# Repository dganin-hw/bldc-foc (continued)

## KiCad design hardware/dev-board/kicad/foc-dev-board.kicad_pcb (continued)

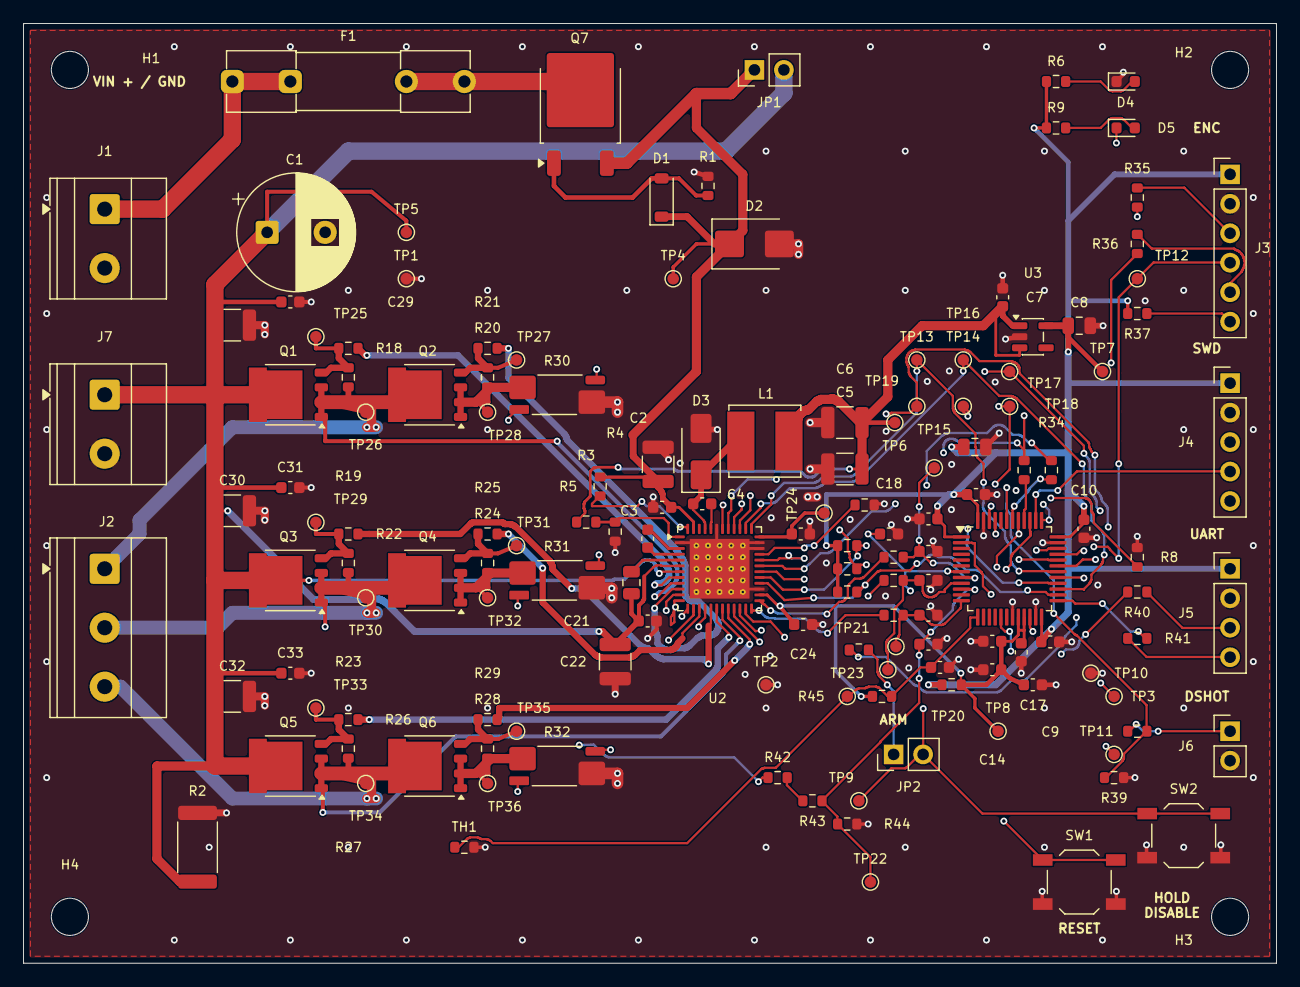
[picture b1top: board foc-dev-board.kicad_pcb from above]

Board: 4 copper layers, 108.0 x 81.0 mm, 149 parts (0 on the bottom side), 83 nets.

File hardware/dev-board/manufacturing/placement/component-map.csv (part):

Reference,Value,MPN_or_assembly,Footprint,X_from_left_mm,Y_from_top_mm,KiCad_angle_deg,Side,Physical_BOM,DNP,Note
C1,470u / 35V low ESR,EEUFR1V471,Capacitor_THT:CP_Radial_D10.0mm_P5.00mm,21.0,18.0,0.0,TOP,True,False,"Panasonic FR, 470uF 35V, D10 x H16 mm, lead pitch 5mm; 0.6mm leads."
C10,100n / 10V,CL10B104KB8NNNC,Capacitor_SMD:C_0603_1608Metric,91.4,43.55,-90.0,TOP,True,False,
C11,100n / 10V,CL10B104KB8NNNC,Capacitor_SMD:C_0603_1608Metric,82.1,40.6,0.0,TOP,True,False,
C12,100n / 10V,CL10B104KB8NNNC,Capacitor_SMD:C_0603_1608Metric,78.0,42.7,180.0,TOP,True,False,
C13,4.7u / 10V,CL21B475KPFNNNE,Capacitor_SMD:C_0805_2012Metric,82.0,36.5,0.0,TOP,True,False,
C14,1u / 10V,CL10B105KO8NNNC,Capacitor_SMD:C_0603_1608Metric,83.5,55.7,180.0,TOP,True,False,
C15,100n / 10V,CL10B104KB8NNNC,Capacitor_SMD:C_0603_1608Metric,83.5,53.25,180.0,TOP,True,False,At VDDA pin 21.
C16,100n / 10V,CL10B104KB8NNNC,Capacitor_SMD:C_0603_1608Metric,86.0,54.2,-90.0,TOP,True,False,At VREF+ pin 20.
C17,1u / 10V,CL10B105KO8NNNC,Capacitor_SMD:C_0603_1608Metric,87.0,57.0,0.0,TOP,True,False,At VREF+ pin 20.
C18,100n / 10V,CL10B104KB8NNNC,Capacitor_SMD:C_0603_1608Metric,74.6,44.0,0.0,TOP,True,False,
C19,47n / 50V X7R,CL10B473KB8NNNC,Capacitor_SMD:C_0603_1608Metric,53.8,44.4,90.0,TOP,True,False,
C2,4.7u / 50V X7R,GRM32ER71H475KA88L,Capacitor_SMD:C_1210_3225Metric,54.7,38.0,90.0,TOP,True,False,
C20,1u / 25V X7R,CL21B105KAFNNNE,Capacitor_SMD:C_0805_2012Metric,52.4,48.2,-90.0,TOP,True,False,
C21,100n / 50V,CL10B104KB8NNNC,Capacitor_SMD:C_0603_1608Metric,53.8,51.5,0.0,TOP,True,False,
C22,10u / 50V X7R,GRM32ER71H106KA12L,Capacitor_SMD:C_1210_3225Metric,51.0,55.0,-90.0,TOP,True,False,
C23,1u / 10V,CL10B105KO8NNNC,Capacitor_SMD:C_0603_1608Metric,67.0,44.0,0.0,TOP,True,False,
C24,100n / 10V,CL10B104KB8NNNC,Capacitor_SMD:C_0603_1608Metric,67.2,51.8,0.0,TOP,True,False,
C25,1n / C0G,GRM1885C1H102JA01D,Capacitor_SMD:C_0603_1608Metric,78.0,45.5,0.0,TOP,True,False,
C26,1n / C0G,GRM1885C1H102JA01D,Capacitor_SMD:C_0603_1608Metric,78.0,51.0,0.0,TOP,True,False,
C27,1n / C0G,GRM1885C1H102JA01D,Capacitor_SMD:C_0603_1608Metric,78.0,48.0,0.0,TOP,True,False,
C28,4.7u / 50V X7R,GRM32ER71H475KA88L,Capacitor_SMD:C_1210_3225Metric,18.0,26.0,0.0,TOP,True,False,
C29,100n / 50V,CL10B104KB8NNNC,Capacitor_SMD:C_0603_1608Metric,23.0,24.0,0.0,TOP,True,False,
C3,100n / 50V,CL10B104KB8NNNC,Capacitor_SMD:C_0603_1608Metric,55.05,41.7,180.0,TOP,True,False,
C30,4.7u / 50V X7R,GRM32ER71H475KA88L,Capacitor_SMD:C_1210_3225Metric,18.0,42.0,0.0,TOP,True,False,
C31,100n / 50V,CL10B104KB8NNNC,Capacitor_SMD:C_0603_1608Metric,23.0,40.0,0.0,TOP,True,False,
C32,4.7u / 50V X7R,GRM32ER71H475KA88L,Capacitor_SMD:C_1210_3225Metric,18.0,58.0,0.0,TOP,True,False,
C33,100n / 50V,CL10B104KB8NNNC,Capacitor_SMD:C_0603_1608Metric,23.0,56.0,0.0,TOP,True,False,
C34,10n / 50V,CL10B103KB8NNNC,Capacitor_SMD:C_0603_1608Metric,78.0,53.5,0.0,TOP,True,False,
C35,10n / 10V,CL10B103KB8NNNC,Capacitor_SMD:C_0603_1608Metric,79.0,55.5,0.0,TOP,True,False,
C4,100n / 25V,CL10B104KB8NNNC,Capacitor_SMD:C_0603_1608Metric,58.5,41.4,180.0,TOP,True,False,
C5,22u / 16V X7R,CL32B226KAJNNNE,Capacitor_SMD:C_1210_3225Metric,70.8,34.4,180.0,TOP,True,False,
C6,22u / 16V X7R,CL32B226KAJNNNE,Capacitor_SMD:C_1210_3225Metric,70.8,38.4,180.0,TOP,True,False,
C7,1u / 10V,CL10B105KO8NNNC,Capacitor_SMD:C_0603_1608Metric,84.4,23.6,90.0,TOP,True,False,
C8,4.7u / 10V,CL21B475KPFNNNE,Capacitor_SMD:C_0805_2012Metric,91.0,26.05,0.0,TOP,True,False,
C9,100n / 10V,CL10B104KB8NNNC,Capacitor_SMD:C_0603_1608Metric,88.5,53.3,0.0,TOP,True,False,
D1,BZT52C12,BZT52C12-7-F,Diode_SMD:D_SOD-123,55.0,15.0,90.0,TOP,True,False,12 V VGS clamp; cathode at PMOS source.
D2,SMBJ18A,SMBJ18A,Diode_SMD:D_SMB,63.0,19.0,0.0,TOP,True,False,"Input transient clamp, NOT a continuous braking resistor."
D3,SS16,SS16,Diode_SMD:D_SMA,58.4,36.9,90.0,TOP,True,False,
D4,POWER green,LTST-C190KGKT,LED_SMD:LED_0603_1608Metric,95.0,5.0,0.0,TOP,True,False,
D5,STATUS green,LTST-C190KGKT,LED_SMD:LED_0603_1608Metric,95.0,9.0,0.0,TOP,True,False,
F1,2A fast / DC-rated,BK1/S501-2-R + 01110005MR x2,Fuse:Fuseholder_Clip-5x20mm_Littelfuse_111_Inline_P20.00x5.00mm_D1.05mm_Horizontal,18.0,5.0,0.0,TOP,True,False,"Assembly: two Littelfuse 111 clips plus one Eaton BK1/S501-2-R, 2A fast 5x20mm cartridge; not a phase-current limiter."
H1,M3 NPTH,,MountingHole:MountingHole_3.2mm_M3,4.0,4.0,0.0,TOP,False,False,
H2,M3 NPTH,,MountingHole:MountingHole_3.2mm_M3,104.0,4.0,0.0,TOP,False,False,
H3,M3 NPTH,,MountingHole:MountingHole_3.2mm_M3,104.0,77.0,0.0,TOP,False,False,
H4,M3 NPTH,,MountingHole:MountingHole_3.2mm_M3,4.0,77.0,0.0,TOP,False,False,
J1,VIN 12V / GND,1715721,"TerminalBlock_Phoenix:TerminalBlock_Phoenix_MKDS-1,5-2-5.08_1x02_P5.08mm_Horizontal",7.0,16.0,-90.0,TOP,True,False,Phoenix MKDS 1.5/2-5.08; wire entry faces board left edge.
J2,MOTOR A / B / C,1715734,"TerminalBlock_Phoenix:TerminalBlock_Phoenix_MKDS-1,5-3-5.08_1x03_P5.08mm_Horizontal",7.0,47.0,-90.0,TOP,True,False,Phoenix MKDS 1.5/3-5.08; wire entry faces board left edge.
J3,ENC 3V3 GND SCK MISO MOSI CS,B-2100S06P-A110,Connector_PinHeader_2.54mm:PinHeader_1x06_P2.54mm_Vertical,104.0,13.0,0.0,TOP,True,False,
J4,SWD VTREF GND IO CLK RESET,B-2100S05P-A110,Connector_PinHeader_2.54mm:PinHeader_1x05_P2.54mm_Vertical,104.0,31.0,0.0,TOP,True,False,
J5,UART 3V3 GND TX RX,B-2100S04P-A110,Connector_PinHeader_2.54mm:PinHeader_1x04_P2.54mm_Vertical,104.0,47.0,0.0,TOP,True,False,
J6,DSHOT / GND,B-2100S02P-A110,Connector_PinHeader_2.54mm:PinHeader_1x02_P2.54mm_Vertical,104.0,61.0,0.0,TOP,True,False,
J7,EXTERNAL BUS LOAD,1715721,"TerminalBlock_Phoenix:TerminalBlock_Phoenix_MKDS-1,5-2-5.08_1x02_P5.08mm_Horizontal",7.0,32.0,-90.0,TOP,True,False,External VM/GND load connection; braking load is not included.
JP1,BRIDGE POWER LINK,B-2100S02P-A110,Connector_PinHeader_2.54mm:PinHeader_1x02_P2.54mm_Vertical,63.0,4.0,90.0,TOP,True,False,
JP2,ARM LINK,B-2100S02P-A110,Connector_PinHeader_2.54mm:PinHeader_1x02_P2.54mm_Vertical,75.0,63.0,90.0,TOP,True,False,
L1,33u / SRN6045TA-330M,SRN6045TA-330M,Inductor_SMD:L_Bourns_SRN6045TA,63.9,36.0,0.0,TOP,True,False,
Q1,PSMN7R0-60YS,"PSMN7R0-60YS,115",Package_TO_SOT_SMD:LFPAK56,23.0,32.0,180.0,TOP,True,False,
Q2,PSMN7R0-60YS,"PSMN7R0-60YS,115",Package_TO_SOT_SMD:LFPAK56,35.0,32.0,180.0,TOP,True,False,
Q3,PSMN7R0-60YS,"PSMN7R0-60YS,115",Package_TO_SOT_SMD:LFPAK56,23.0,48.0,180.0,TOP,True,False,
Q4,PSMN7R0-60YS,"PSMN7R0-60YS,115",Package_TO_SOT_SMD:LFPAK56,35.0,48.0,180.0,TOP,True,False,
Q5,PSMN7R0-60YS,"PSMN7R0-60YS,115",Package_TO_SOT_SMD:LFPAK56,23.0,64.0,180.0,TOP,True,False,
Q6,PSMN7R0-60YS,"PSMN7R0-60YS,115",Package_TO_SOT_SMD:LFPAK56,35.0,64.0,180.0,TOP,True,False,
Q7,IRFR5305TRPBF,IRFR5305TRPBF,Package_TO_SOT_SMD:TO-252-2,48.0,7.0,90.0,TOP,True,False,"Reverse polarity: drain toward input, source toward load. On-state permits regenerative current to source."
R1,10k,RC0603FR-0710KL,Resistor_SMD:R_0603_1608Metric,59.0,14.0,90.0,TOP,True,False,
R10,1k,RC0603FR-071KL,Resistor_SMD:R_0603_1608Metric,71.0,45.0,0.0,TOP,True,False,Open-drain SDO; verify RC rise time with encoder cable. 3.3mA maximum static load.
R11,10k,RC0603FR-0710KL,Resistor_SMD:R_0603_1608Metric,71.0,47.0,0.0,TOP,True,False,
R12,10k,RC0603FR-0710KL,Resistor_SMD:R_0603_1608Metric,71.0,49.0,0.0,TOP,True,False,
R13,1k,RC0603FR-071KL,Resistor_SMD:R_0603_1608Metric,72.0,54.0,0.0,TOP,True,False,
R14,10k,RC0603FR-0710KL,Resistor_SMD:R_0603_1608Metric,72.5,41.5,0.0,TOP,True,False,
R15,100R,RC0603FR-07100RL,Resistor_SMD:R_0603_1608Metric,75.0,46.0,0.0,TOP,True,False,
R16,100R,RC0603FR-07100RL,Resistor_SMD:R_0603_1608Metric,75.0,51.0,0.0,TOP,True,False,
R17,100R,RC0603FR-07100RL,Resistor_SMD:R_0603_1608Metric,75.0,48.0,0.0,TOP,True,False,
R18,2.2R,RC0603FR-072R2L,Resistor_SMD:R_0603_1608Metric,28.0,28.0,180.0,TOP,True,False,
R19,100k,RC0603FR-07100KL,Resistor_SMD:R_0603_1608Metric,28.0,30.5,-90.0,TOP,True,False,
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
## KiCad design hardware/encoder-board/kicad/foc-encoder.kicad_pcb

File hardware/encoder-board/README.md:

# Плата энкодера

Маленькая плата с датчиком AS5047P. Она измеряет угол ротора по магниту на валу
мотора и передаёт его в STM32 основной платы по SPI. На плате восемь компонентов:
датчик, два конденсатора, четыре резистора и разъём.

*Слева сторона, обращённая к магниту, справа обратная сторона с разъёмом.*

## Коротко

| Параметр | Значение |
|---|---|
| Размер | 32 × 28 мм, 2 слоя, FR-4 1,6 мм, фаски 1 мм на углах |
| Датчик | AS5047P-ATSM, 14 бит, TSSOP-14, в центре платы |
| Питание | только 3,3 В от основной платы (3,0-3,6 В), 5 В подавать нельзя |
| Интерфейс | SPI mode 1, первые запуски на частоте до 1 МГц |
| Крепление | 4 отверстия Ø2,2 мм под M2 на сетке 24 × 20 мм, по центру датчика |
| Разъём | JST GH, 6 контактов, на обратной стороне |

## Подключение к основной плате

| Основная плата, J3 | Энкодер, J1 | Сигнал | Вывод AS5047P |
|---:|---:|---|---|
| 1 | 1 | 3,3 В | 11 и 12 (соединены) |
| 2 | 2 | GND | 5 (TEST) и 13 |
| 3 | 3 | SCK | 2 |
| 4 | 4 | MISO | 3, через R4 33 Ом |
| 5 | 5 | MOSI | 4 |
| 6 | 6 | CS, активный ноль | 1 |

Разъём J1 - JST SM06B-GHS-TB(LF)(SN), шаг 1,25 мм. Ответная часть - корпус
GHR-06V-S и шесть контактов SSHL-002T-P0.2. На другом конце кабеля гнездовая колодка
1×6 с шагом 2,54 мм под J3. Готовый кабель GH-GH сюда не подходит.

- Для первого кабеля провод AWG28 длиной до 150 мм. Это условие для стенда, а не
  гарантированная длина линии SPI.
- Контакты считать по маркировке платы и чертежу разъёма, а не по цвету провода.
  Вид сзади зеркальный.
- До включения прозвонить все шесть проводов и проверить, что соседние контакты
  не замкнуты.
- Кабель вести подальше от фазных проводов мотора.

Контрольные площадки: TP1 - 3,3 В, TP2 - GND, TP3 - CS, TP4 - SCK, TP5 - MOSI,
TP6 - MISO после R4.

## Схема

- Выводы питания VDD (11) и VDD3V3 (12) соединены, как требует питание 3,3 В.
  TEST (5) соединён с GND (13). Рядом стоят C1 100 нФ и C2 1 мкФ.
- R1 10 кОм держит CS в единице, R2 и R3 47 кОм держат SCK и MOSI в нуле, пока
  STM32 в сбросе. Вместе с R37 10 кОм на основной плате CS подтянут примерно через
  5 кОм.
- R4 33 Ом стоит у выхода MISO. Линия MISO общая с DRV8323 на основной плате, там
  же подтяжка R10 1 кОм. При CS = 1 датчик отпускает линию. Энкодер и драйвер нельзя
  выбирать одновременно.
- Выходы A/B/I и U/V/W датчика не используются.

## Первый запуск

1. Обесточить обе платы. Проверить ориентацию U1, пайку, отсутствие перемычек
   припоем, соединение выводов 11 и 12, TEST и GND. Прозвонить кабель.
2. Подать питание на основную плату при снятой JP1, чтобы мост был обесточен.
   Измерить 3,3 В между TP1 и TP2, проверить, что ничего не греется. Датчик
   потребляет до 15 мА.
3. Настроить SPI: mode 1 (CPOL = 0, CPHA = 1), старшим битом вперёд, 16 бит,
   частота до 1 МГц. После включения подождать 10 мс. От спада CS до первого такта
   и между посылками при CS = 1 выдерживать не меньше 350 нс.
4. Ответ приходит со сдвигом на одну посылку: сначала команда чтения, ответ на неё
   придёт в следующей посылке. Команды отправлять с чётным битом чётности, в ответе
   проверять чётность и флаг ошибки.
5. Прочитать регистры диагностики и угол при медленном полном обороте. Переход
   16383 → 0 при прохождении нуля нормален. Проверить повторяемость и биение,
   положение магнита подобрать по диагностике поля.
6. Ноль электрического угла и направление вращения хранить в прошивке STM32.
   OTP-память датчика для стенда программировать не нужно.

Паспортные 10 МГц SPI на стенде не проверялись.

## Механика

| Элемент | Координаты в KiCad, мм | Относительно U1, мм |
|---|---|---|
| U1, ось магнита | 100; 100 | 0; 0 |
| H1, Ø2,2 | 88; 90 | -12; -10 |
| H2, Ø2,2 | 112; 90 | +12; -10 |
| H3, Ø2,2 | 112; 110 | +12; +10 |
| H4, Ø2,2 | 88; 110 | -12; +10 |
| J1, обратная сторона | 100; 110,5 | 0; +10,5 |

Вид со стороны магнита: X вправо, Y вниз.

- Сторона `MAGNET SIDE` смотрит на магнит, кабель выходит у нижнего края с обратной
  стороны.
- Плата крепится к неподвижному кронштейну, а не к вращающемуся торцу мотора.
  Головки винтов, шайбы и стойки не шире Ø4,5 мм, вокруг отверстий зона без меди
  Ø5 мм. Крепёж лучше немагнитный, например латунный. Не всякая нержавейка немагнитна.
- Магнит двухполюсный, намагниченный по диаметру, Ø6 × 2,5 мм. По документации
  датчику нужно поле 35-70 мТ. Начальный зазор 2 мм от крышки магнита до корпуса U1
  задаётся калибром из комплекта стенда, рабочий зазор подбирается по диагностике.
- Позади платы у J1 нужно около 6 мм свободного места и около 15 мм за краем платы
  для колодки, проводов и защёлки.

Плата и магнит встроены в [испытательный стенд](../stand/README.md).

## Файлы

- [`kicad/`](kicad/) - проект KiCad 10, открывать `foc-encoder.kicad_pro`.
- [`documentation/SCHEMATIC.pdf`](documentation/SCHEMATIC.pdf) - схема.
- [`documentation/ASSEMBLY-TOP.pdf`](documentation/ASSEMBLY-TOP.pdf) и
  [`ASSEMBLY-BOTTOM.pdf`](documentation/ASSEMBLY-BOTTOM.pdf) - сборочные чертежи.
- [`manufacturing/`](manufacturing/) - Gerber, сверловка, перечень компонентов и координаты.
- [`mechanical/foc-encoder.step`](mechanical/foc-encoder.step) - 3D-модель с компонентами,
  начало координат XY на оси U1. При импорте проверить направление осей и Z.
- [`mechanical/`](mechanical/) - контур и оси в DXF.

Проверки ERC и DRC в KiCad проходят без ошибок. SPI, магнит и механику ещё нужно
проверить на собранной плате.

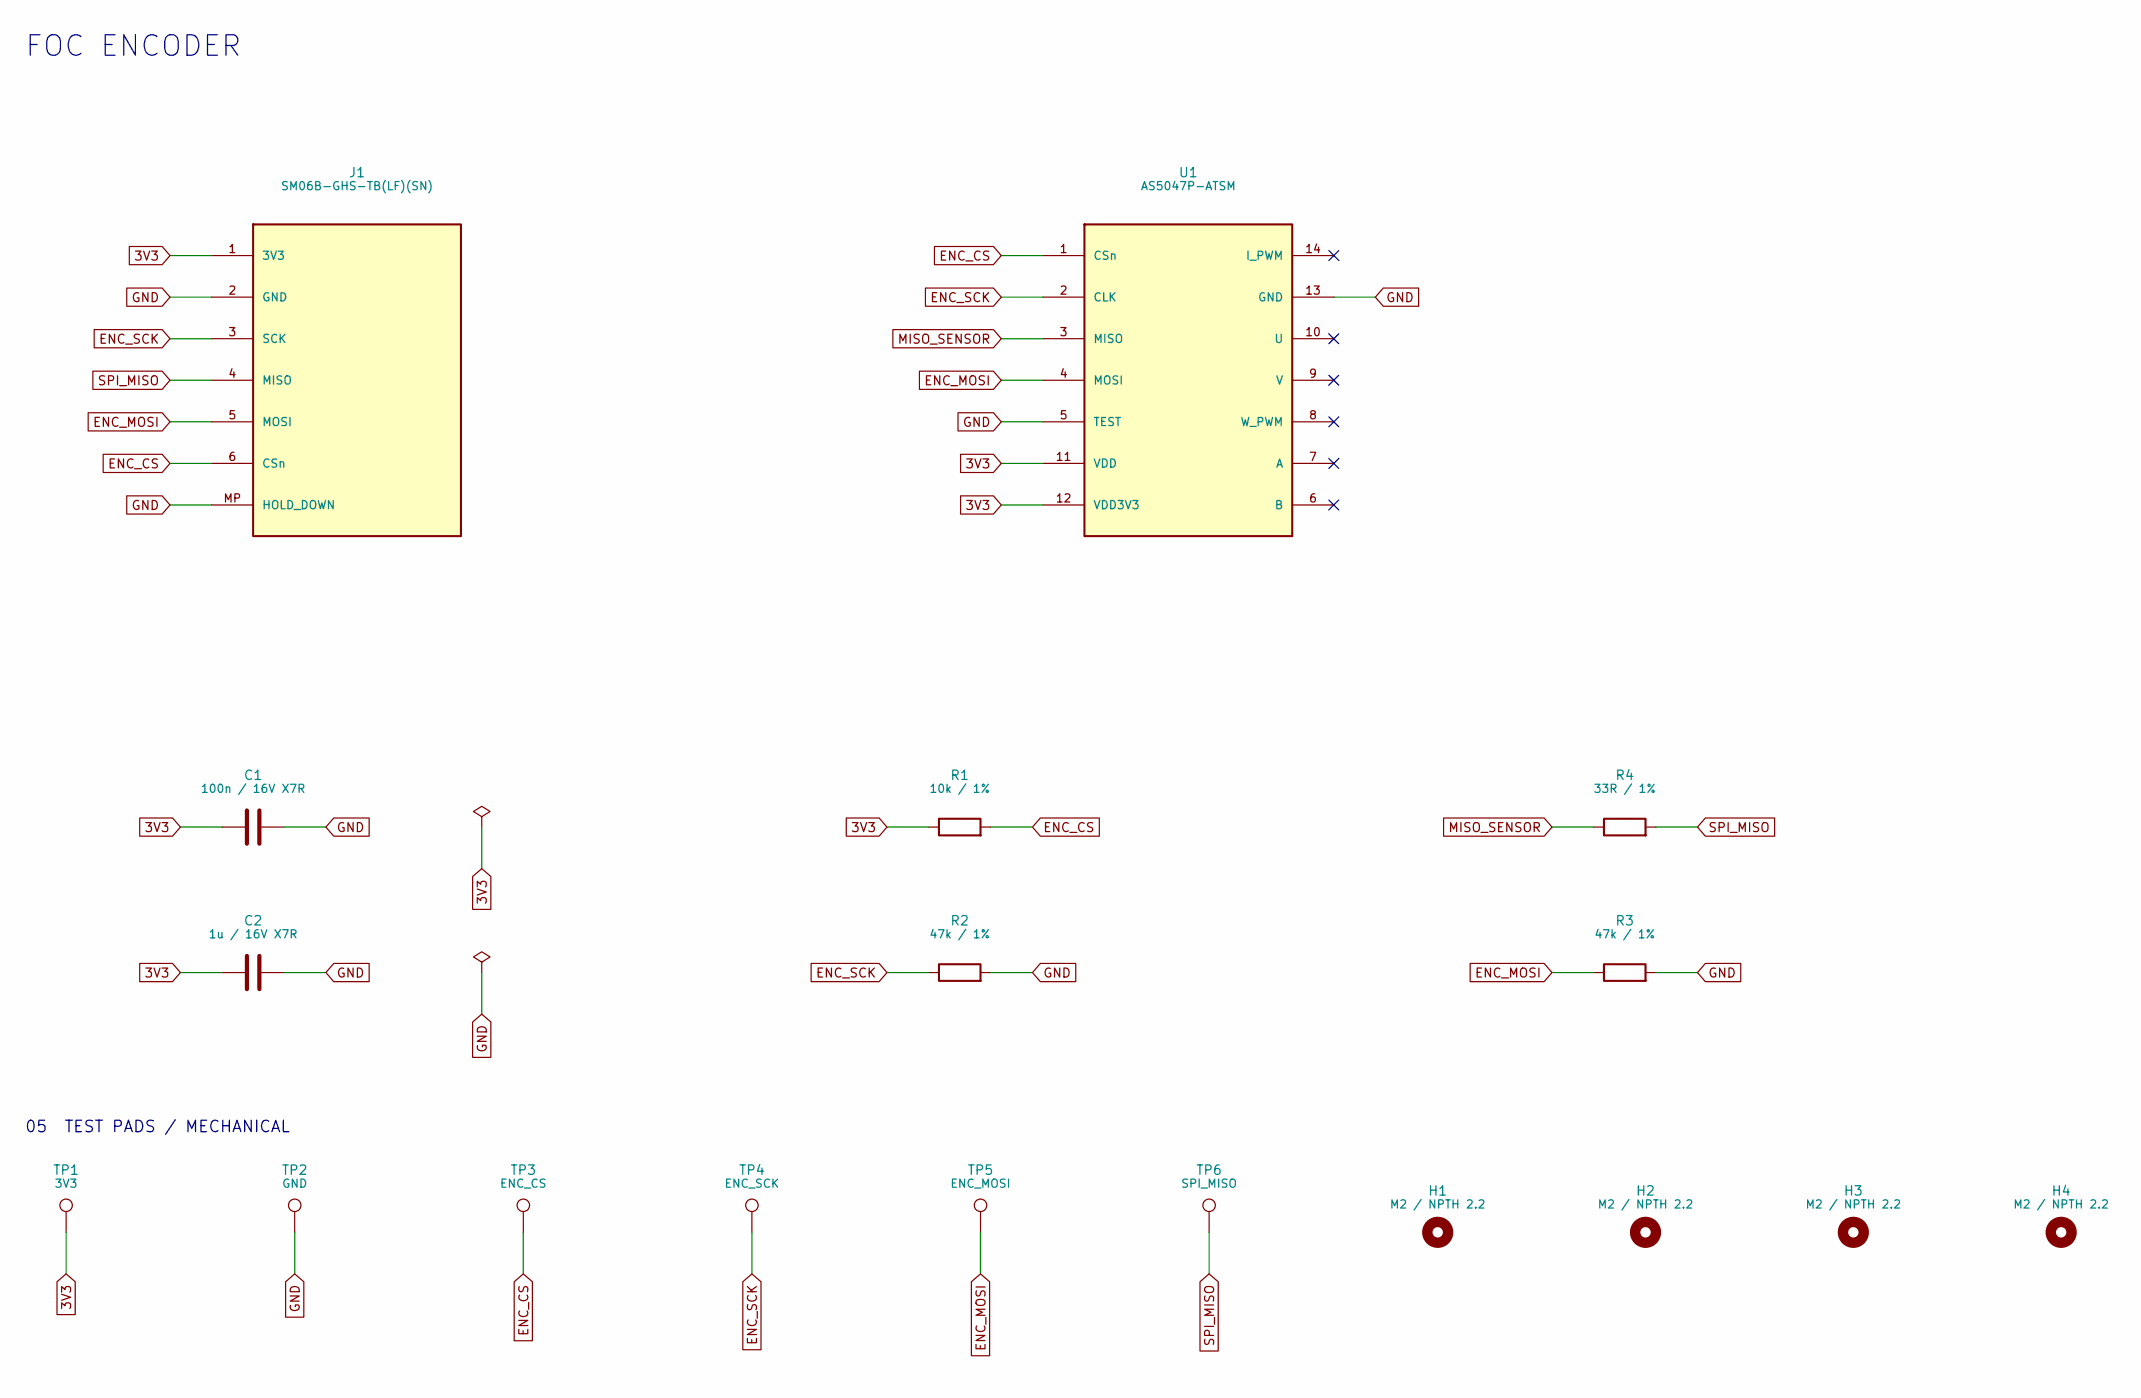
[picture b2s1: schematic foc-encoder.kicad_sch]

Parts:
C1: 100n / 16V X7R; C_0603_1608Metric; MPN CL10B104KB8NNNC
C2: 1u / 16V X7R; C_0603_1608Metric; MPN CL10B105KO8NNNC
H1, H2, H3, H4: M2 / NPTH 2.2; MountingHole_2.2mm_M2
J1: SM06B-GHS-TB(LF)(SN); JST_GH_SM06B-GHS-TB_1x06-1MP_P1.25mm_Horizontal; MPN SM06B-GHS-TB(LF)(SN)
R1: 10k / 1%; R_0603_1608Metric; MPN RC0603FR-0710KL
R2, R3: 47k / 1%; R_0603_1608Metric; MPN RC0603FR-0747KL
R4: 33R / 1%; R_0603_1608Metric; MPN RC0603FR-0733RL
TP1: 3V3; TestPoint_Pad_D1.0mm
TP2: GND; TestPoint_Pad_D1.0mm
TP3: ENC_CS; TestPoint_Pad_D1.0mm
TP4: ENC_SCK; TestPoint_Pad_D1.0mm
TP5: ENC_MOSI; TestPoint_Pad_D1.0mm
TP6: SPI_MISO; TestPoint_Pad_D1.0mm
U1: AS5047P-ATSM; TSSOP-14_4.4x5mm_P0.65mm; MPN AS5047P-ATSM

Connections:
3V3: C1.1, C2.1, J1.1 (3V3), R1.1, TP1.1, U1.11 (VDD), U1.12 (VDD3V3)
ENC_CS: J1.6 (CSn), R1.2, TP3.1, U1.1 (CSn)
ENC_MOSI: J1.5 (MOSI), R3.1, TP5.1, U1.4 (MOSI)
ENC_SCK: J1.3 (SCK), R2.1, TP4.1, U1.2 (CLK)
GND: C1.2, C2.2, J1.2 (GND), J1.MP (HOLD_DOWN), R2.2, R3.2, TP2.1, U1.5 (TEST), U1.13 (GND)
MISO_SENSOR: R4.1, U1.3 (MISO)
SPI_MISO: J1.4 (MISO), R4.2, TP6.1

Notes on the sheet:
05 TEST PADS / MECHANICAL
FOC ENCODER

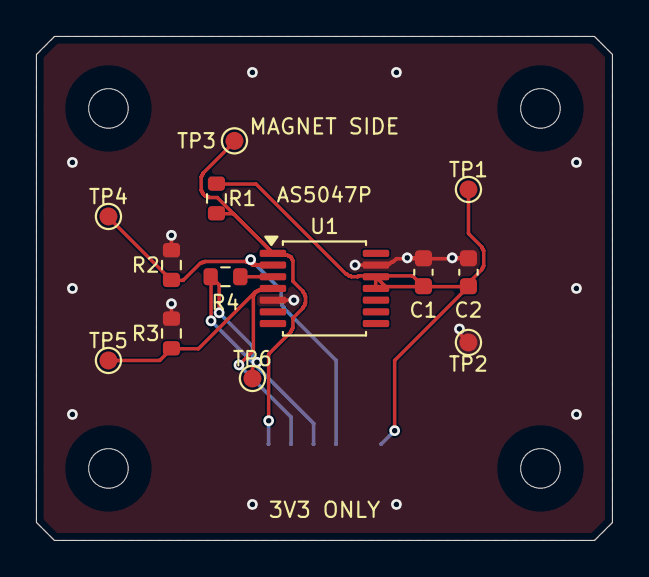
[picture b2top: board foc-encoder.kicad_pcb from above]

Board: 2 copper layers, 32.0 x 28.0 mm, 18 parts (1 on the bottom side), 7 nets.

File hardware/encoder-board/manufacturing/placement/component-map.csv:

Ref,Value,MPN,X_mm,Y_mm,Rotation_deg,Side,In_BOM
C1,100n / 16V X7R,CL10B104KB8NNNC,105.5,99.1,90.0,Top,True
C2,1u / 16V X7R,CL10B105KO8NNNC,108.0,99.1,90.0,Top,True
H1,M2 / NPTH 2.2,,88.0,90.0,0.0,Top,False
H2,M2 / NPTH 2.2,,112.0,90.0,0.0,Top,False
H3,M2 / NPTH 2.2,,112.0,110.0,0.0,Top,False
H4,M2 / NPTH 2.2,,88.0,110.0,0.0,Top,False
J1,SM06B-GHS-TB(LF)(SN),SM06B-GHS-TB(LF)(SN),100.0,110.5,180.0,Bottom,True
R1,10k / 1%,RC0603FR-0710KL,94.0,95.0,-90.0,Top,True
R2,47k / 1%,RC0603FR-0747KL,91.5,98.7,90.0,Top,True
R3,47k / 1%,RC0603FR-0747KL,91.5,102.5,90.0,Top,True
R4,33R / 1%,RC0603FR-0733RL,94.5,99.35,180.0,Top,True
TP1,3V3,,108.0,94.5,0.0,Top,False
TP2,GND,,108.0,103.0,0.0,Top,False
TP3,ENC_CS,,95.0,91.8,0.0,Top,False
TP4,ENC_SCK,,88.0,96.0,0.0,Top,False
TP5,ENC_MOSI,,88.0,104.0,0.0,Top,False
TP6,SPI_MISO,,96.0,105.0,0.0,Top,False
U1,AS5047P-ATSM,AS5047P-ATSM,100.0,100.0,0.0,Top,True

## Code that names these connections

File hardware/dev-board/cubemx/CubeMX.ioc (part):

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Mcu.Name=STM32G431C(6-8-B)Tx
Mcu.Package=LQFP48
Mcu.UserName=STM32G431CBTx
PA0.Mode=IN1-Single-Ended
PA0.Signal=ADC1_IN1
PA1.Mode=IN2-Single-Ended
PA1.Signal=ADC1_IN2
PA10.GPIOParameters=GPIO_Speed
PA10.GPIO_Speed=GPIO_SPEED_FREQ_VERY_HIGH
PA10.Signal=S_TIM1_CH3
PA11.GPIOParameters=GPIO_Label
PA11.GPIO_Label=DRV_ENABLE
PA11.Signal=GPIO_Output
PA12.GPIOParameters=GPIO_PuPd,GPIO_Label,GPIO_ModeDefaultEXTI
PA12.GPIO_Label=DRV_NFAULT
PA12.GPIO_ModeDefaultEXTI=GPIO_MODE_IT_FALLING
PA12.GPIO_PuPd=GPIO_PULLUP
PA12.Signal=GPXTI12
PA13.Mode=Serial_Wire
PA13.Signal=SYS_JTMS-SWDIO
PA14.Mode=Serial_Wire
PA14.Signal=SYS_JTCK-SWCLK
PA15.GPIOParameters=PinState,GPIO_Label
PA15.GPIO_Label=DRV_CS
PA15.PinState=GPIO_PIN_SET
PA15.Signal=GPIO_Output
PA2.Mode=IN3-Single-Ended
PA2.Signal=ADC1_IN3
PA4.Mode=IN17-Single-Ended
PA4.Signal=ADC2_IN17
PA5.Mode=IN13-Single-Ended
PA5.Signal=ADC2_IN13
PA8.GPIOParameters=GPIO_Speed
PA8.GPIO_Speed=GPIO_SPEED_FREQ_VERY_HIGH
PA8.Signal=S_TIM1_CH1
PA9.GPIOParameters=GPIO_Speed
PA9.GPIO_Speed=GPIO_SPEED_FREQ_VERY_HIGH
PA9.Signal=S_TIM1_CH2
PB1.GPIOParameters=GPIO_Label
PB1.GPIO_Label=TP_TIMING
PB1.Signal=GPIO_Output
PB10.Mode=Asynchronous
PB10.Signal=USART3_TX
PB11.Mode=Asynchronous
PB11.Signal=USART3_RX
PB12.Mode=Activate-Break-Input
PB12.Signal=TIM1_BKIN
PB13.GPIOParameters=GPIO_Speed
PB13.GPIO_Speed=GPIO_SPEED_FREQ_VERY_HIGH
PB13.Mode=PWM Generation1 CH1 CH1N
PB13.Signal=TIM1_CH1N
PB14.GPIOParameters=GPIO_Speed
PB14.GPIO_Speed=GPIO_SPEED_FREQ_VERY_HIGH
PB14.Mode=PWM Generation2 CH2 CH2N
PB14.Signal=TIM1_CH2N
PB15.GPIOParameters=GPIO_Speed
PB15.GPIO_Speed=GPIO_SPEED_FREQ_VERY_HIGH
PB15.Mode=PWM Generation3 CH3 CH3N
PB15.Signal=TIM1_CH3N
PB3.GPIOParameters=GPIO_Speed
PB3.GPIO_Speed=GPIO_SPEED_FREQ_HIGH
PB3.Mode=Full_Duplex_Master
PB3.Signal=SPI1_SCK
PB4.GPIOParameters=GPIO_Speed
PB4.GPIO_Speed=GPIO_SPEED_FREQ_HIGH
PB4.Mode=Full_Duplex_Master
PB4.Signal=SPI1_MISO
PB5.GPIOParameters=GPIO_Speed
PB5.GPIO_Speed=GPIO_SPEED_FREQ_HIGH
PB5.Mode=Full_Duplex_Master
PB5.Signal=SPI1_MOSI
PB6.Signal=S_TIM4_CH1
PB9.GPIOParameters=PinState,GPIO_Label
PB9.GPIO_Label=ENC_CS
PB9.PinState=GPIO_PIN_SET
PB9.Signal=GPIO_Output
PC13.GPIOParameters=GPIO_Label
PC13.GPIO_Label=LED
PC13.Signal=GPIO_Output
RCC.HSE_VALUE=8000000
RCC.SYSCLKFreq_VALUE=170000000
RCC.SYSCLKSource=RCC_SYSCLKSOURCE_PLLCLK
board=custom
